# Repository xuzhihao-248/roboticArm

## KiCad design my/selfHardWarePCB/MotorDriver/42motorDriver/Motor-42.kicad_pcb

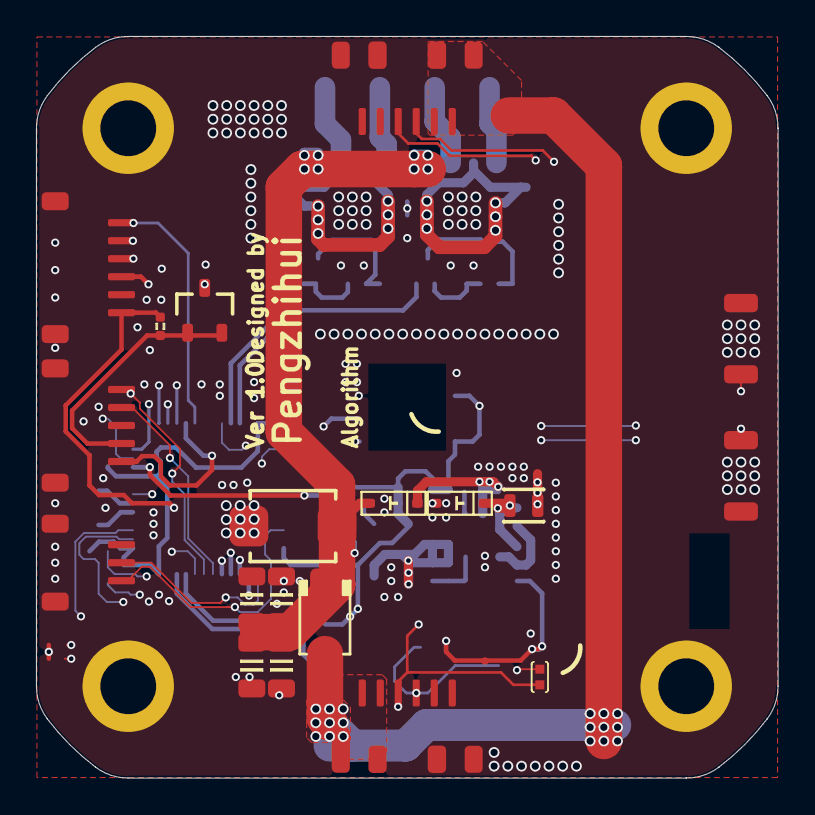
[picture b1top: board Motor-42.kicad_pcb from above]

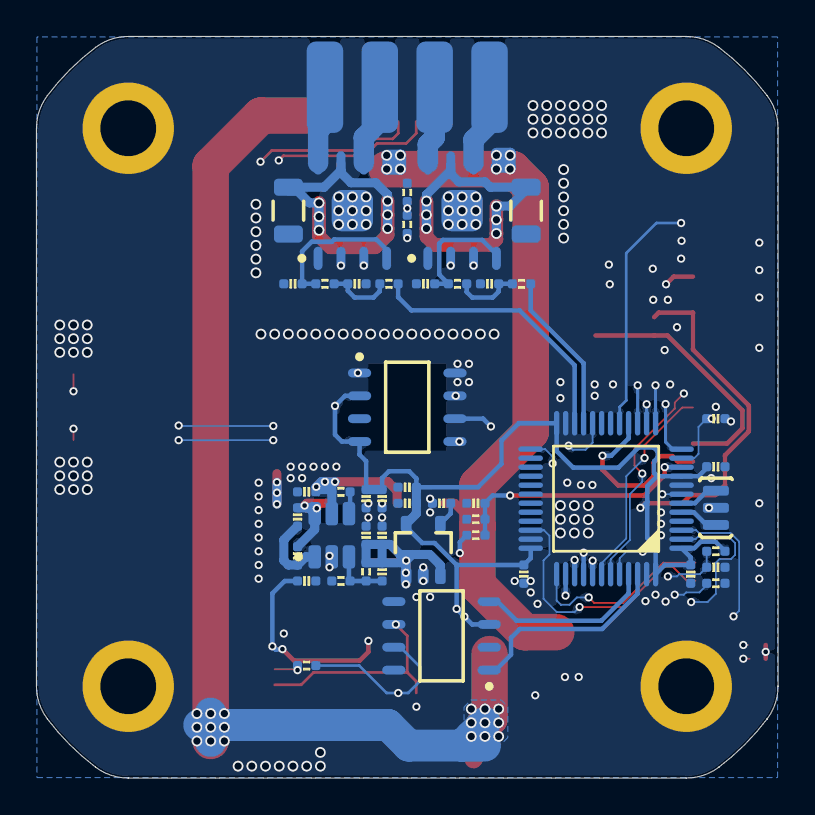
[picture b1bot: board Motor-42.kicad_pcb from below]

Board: 4 copper layers, 41.2 x 41.2 mm, 67 parts (46 on the bottom side), 47 nets.

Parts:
C1, C2, C4, C5, C6, C7, C8, C9, C15, C17, C18, C21, C25, C26: 0.1uF; CAP_0402
C3, C10, C19, C22, C24: 10uF; CAP_0402
C11, C12, C13, C14: 100uF; 1206-CAP
C16: 100pF; CAP_0402
C20: 10uF/50V; CAP_0402
C23: 10nF; CAP_0402
D1: SS54; DO-214AC
D2: SMBJ28CA; SMBJ-CA_MFG
D3, D4: 二极管-5819W; SOD-323
J1: 跳线; 0402-0R
K1, K2: TACT 2P; ButtonTACT_3x4x2_180
L1: 6.8uH; IND-201612
P1: SH1.0-5P
P2, P3, P4: SH1.0-6P
P5: SH1.0-3P
R1, R2, R6, R7, R17: 1K; RES_0402
R3, R8: 0.1R; 1206-RES
R4: NCP15XH103F03RC; RES_0402
R5: 3.3K; RES_0402
R9, R10, R13, R16: 10K; RES_0402
R11, R12: 120R; RES_0402
R14: 1.8K; RES_0402
R15: 1M; RES_0402
T1, T2: 测试点; TEST_PT
U1, U2: TB67H450FNG; SO-8-PAD
U3: STM32F103CBT6; LQFP-48
U4: TL431IDBZT; SOT23-3
U5: SN65HVD232D; SO-8
U6: ME3116; SOT23-6
U7: LP2992 3V3; SOT23-5
U8: MT6816; SO-8
Y1: 12MHz; 晶振-3P

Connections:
ADC_ENC: P1.5, U3.16
BUTTON_1: K1.2, U3.25
BUTTON_2: K2.2, U3.20
CAN_H: P2.4, P3.4, R12.1, U5.7
CAN_L: J1.2, P2.3, P3.3, U5.6
CAN_RX: U3.45, U5.4
CAN_TX: U3.46, U5.1
GND: C1.1, C2.1, C3.1, C4.1, C5.1, C6.1, C7.1, C8.1, C9.1, C10.1, C11.1, C12.1, C13.1, C14.1, C18.1, C19.1, C20.1, C21.1, C22.1, C23.1, C24.1, C25.1, C26.1, D2.1, D3.1, K1.1, K2.1, P1.3, P1.SH1, P1.SH2, P2.5, P2.6, P2.SH2, P3.5, P3.6, P3.SH2, P4.5, P4.SH1, P4.SH2, P5.1, P5.SH1, P5.SH2, R3.2, R5.1, R8.2, R9.2, R14.1, R17.2, U1.1, U1.9, U2.1, U2.9, U3.8, U3.23, U3.35, U3.47, U4.3, U5.2, U6.2, U7.2, U8.8, Y1.2
IN_AM: U1.2, U3.14
IN_AP: U1.3, U3.15
IN_BM: U2.2, U3.12
IN_BP: U2.3, U3.13
IN_PWM_A: R1.1, U3.22
IN_PWM_B: R6.1, U3.21
MT6816_AUX_CS: P4.1, U3.17
MT6816_CS: U3.38, U8.1
NetC1_2: C1.2, R1.2, R2.1
NetC4_2: C4.2, R6.2, R7.1
NetC9_2: C9.2, R10.1, U3.7
NetC15_1: C15.1, C17.1, D3.2, L1.1, U6.6
NetC15_2: C15.2, C17.2, U6.1
NetC16_2: C16.2, R13.1, R14.2, U6.3
NetC20_2: C20.2, D4.2, R15.1, U6.5
NetC23_2: C23.2, U7.4
NetJ1_1: J1.1, R12.2
NetP1_4: P1.4, R11.2, U4.1, U4.2
NetR3_1: R3.1, U1.7
NetR8_1: R8.1, U2.7
NetR9_1: R9.1, U3.44
NetR15_2: R15.2, U6.4
NetU3_5: U3.5, Y1.3
NetU3_6: U3.6, Y1.1
POWER_U: C26.2, R16.2, R17.1, U3.10
SPI1_MISO: P4.2, U3.40, U8.6
SPI1_MOSI: P4.3, U3.41, U8.5
SPI1_SCK: P4.4, U3.39, U8.7
SWCLK: P5.2, U3.37
SWDIO: P5.3, U3.34
TEMP: C3.2, R4.1, R5.2, U3.11
UART1_RX: P1.1, U3.43
UART1_TX: P1.2, U3.42
VCC: C11.2, C12.2, C13.2, C14.2, D1.2, D2.2, D4.1, R16.1, U1.5, U2.5
VCC_3V3: C6.2, C7.2, C8.2, C10.2, C21.2, C22.2, C24.2, C25.2, P4.6, R4.2, R10.2, R11.1, T2.0, U3.1, U3.9, U3.24, U3.36, U3.48, U5.3, U7.5, U8.2, U8.4
VCC_5V: C16.1, C18.2, C19.2, L1.2, R13.2, T1.0, U7.1, U7.3
VCC_IN: D1.1, P2.1, P2.2, P2.SH1, P3.1, P3.2, P3.SH1
VREF_A: C2.2, R2.2, U1.4
VREF_B: C5.2, R7.2, U2.4

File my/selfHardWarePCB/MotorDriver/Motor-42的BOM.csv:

Reference,Qty,Value,DNP,Exclude from BOM,Exclude from Board,Footprint,Datasheet
1?,1,OLED-12880,,,,OLED-12880,
"C1,C2,C4,C5,C6,C7,C8,C9,C15,C17,C18,C21,C25,C26,C32",15,0.1uF,,,,CAP_0402,
"C3,C10,C19,C22,C24,C28,C30",7,10uF,,,,CAP_0402,
"C11,C12,C13,C14",4,100uF,,,,1206-CAP,
C16,1,100pF,,,,CAP_0402,
C20,1,10uF/50V,,,,CAP_0402,
C23,1,10nF,,,,CAP_0402,
C33,1,220pF,,,,CAP_0402,
D1,1,SS54,,,,DO-214AC,
D2,1,SMBJ28CA,,,,SMBJ-CA_MFG,
"D3,D4",2,二极管-5819W,,,,SOD-323,
D6,1,二极管-5B5819WS,,,,SOD-323,
J1,1,跳线,,,,0402-0R,
"K1,K2",2,TACT 2P,,,,ButtonTACT_3x4x2_180,
L1,1,6.8uH,,,,IND-201612,
L2,1,2.2uH,,,,2520-L,
P1,1,SH1.0-5P,,,,SH1.0-5P,
"P2,P3,P4",3,SH1.0-6P,,,,SH1.0-6P,
P5,1,SH1.0-3P,,,,SH1.0-3P,
"R1,R2,R6,R7,R17",5,1K,,,,RES_0402,
"R3,R8",2,0.1R,,,,1206-RES,
R4,1,NCP15XH103F03RC,,,,RES_0402,
R5,1,3.3K,,,,RES_0402,
"R9,R10,R13,R16",4,10K,,,,RES_0402,
"R11,R12",2,120R,,,,RES_0402,
R14,1,1.8K,,,,RES_0402,
R15,1,1M,,,,RES_0402,
R23,1,560K,,,,RES_0402,
R26,1,93.1K,,,,RES_0402,
R27,1,13.3K,,,,RES_0402,
"T1,T2",2,测试点,,,,TEST_PT,
"U1,U2",2,TB67H450FNG,,,,SO-8-PAD,
U3,1,STM32F103CBT6,,,,LQFP-48,
U4,1,TL431IDBZT,,,,SOT23-3,
U5,1,SN65HVD232D,,,,SO-8,
U6,1,ME3116,,,,SOT23-6,
U7,1,LP2992 3V3,,,,SOT23-5,
U8,1,MT6816,,,,SO-8,
U11,1,TPS61040DBV,,,,SOT23-5,
Y1,1,12MHz,,,,晶振-3P,

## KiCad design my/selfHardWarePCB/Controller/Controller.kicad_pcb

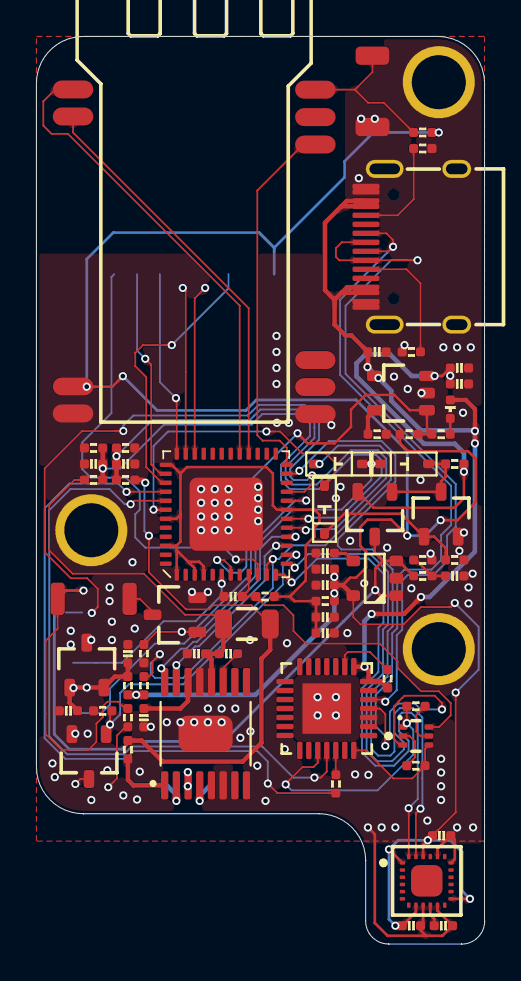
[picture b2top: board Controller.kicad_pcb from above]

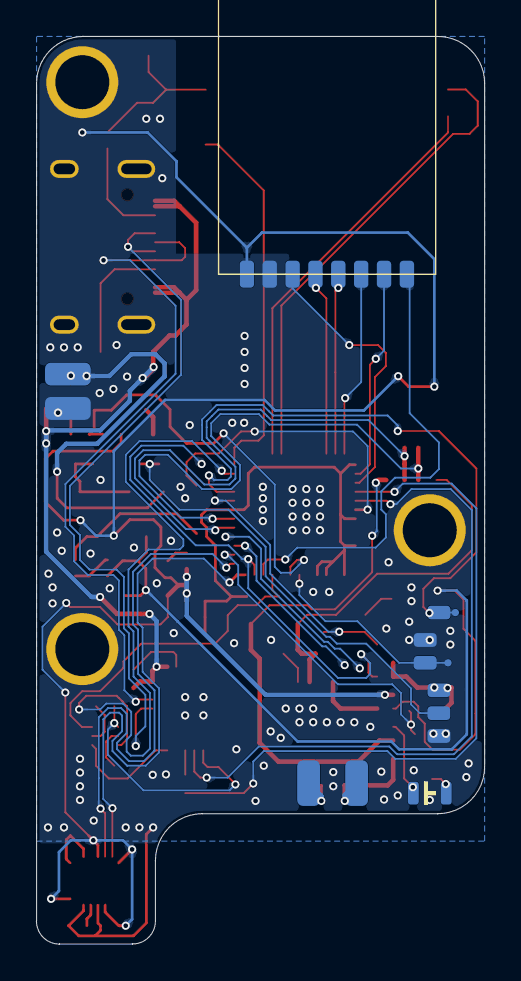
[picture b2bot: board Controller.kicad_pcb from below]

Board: 2 copper layers, 24.9 x 50.4 mm, 71 parts (4 on the bottom side), 60 nets.

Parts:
C1, C5, C13, C15, C17, C19: 0.1uF; CAP_0402
C2, C6, C7, C8, C9, C11, C12, C14, C18: 10uF; CAP_0402
C3: 2.2uF; CAP_0402
C4, C10, C16: 10nF; CAP_0402
C20: 1uF; CAP_0402
D1, D2, D3: 二极管-5819W; SOD-323
D4: color?; LED_0402_RED
D5: color?; LED_0805_RED
K1: TACT 2P; ButtonTACT_3x4x2_180
Q1: AO3401A; SOT23-3
Q2, Q4, Q5: AO3400A; SOT23-3
Q3: BC847BVC-7; SOT563-6
R1, R8, R9, R17, R22, R23, R25, R26, R27: 10K; RES_0402
R2, R4: 100K; RES_0402
R3, R5, R6, R13: 20K; RES_0402
R7: 200R; RES_0402
R10, R24: 47K; RES_0402
R11: 120R; RES_0402
R12: 1R; 1206-RES
R14: 2K; RES_0402
R15, R18: 12K; RES_0402
R16: 1K; RES_0402
R19, R20: 5.1K; RES_0402
R21: 0R; RES_0402
T1, T2: 测试点; TEST_PT
U1: CP2102; QFN-28
U2: LP2992 3V3; SOT23-5
U3: DRV8833PW; TSSOP-16
U4: TL431IDBZT; SOT23-3
U5: MCP73831T; SOT23-5
U6: MPU9250; QFN-24-3x3
U7: DET402
U8: HC-06; 蓝牙模块HC-06
U9: NRF24L01; NRF24L01-MODULE
U10: ESP32_SIP; QFN-48_7X7
USB1: Type-C; Type-C-TOP

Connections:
3V3A: C18.2, C19.2, R21.2, R25.1, U10.1, U10.3, U10.4, U10.19, U10.37, U10.43, U10.46
BAT_DET_1: C5.2, R2.1, R4.2
BOOT_1: Q3.3, U10.23
BT_SET_1: K1.1, R24.2, U8.34
BUZZ_1: Q4.1, R26.2, U10.20
CHG_DET_1: R16.2, R17.1, U5.1, U10.7
CP_Rx_1: U1.25, U10.41
CP_Tx_1: R7.1, U10.40
DTR_1: Q3.4, R15.1, U1.28
EC_KEY_1: D1.2, D2.2
EC_KEY_DET_1: D2.1, R22.2, U10.11
ESP_EN_1: C20.1, Q3.6, R25.2, U10.9
GND: C1.1, C2.1, C3.1, C4.1, C5.1, C6.1, C7.1, C8.1, C9.1, C11.1, C12.1, C13.1, C14.1, C15.2, C16.2, C17.1, C18.1, C19.1, C20.2, K1.2, Q2.2, Q4.2, Q5.2, R4.1, R8.1, R9.1, R13.1, R14.2, R19.1, R20.2, R26.1, R27.1, U1.3, U1.29, U2.2, U3.3, U3.6, U3.13, U3.PAD, U4.3, U5.2, U6.9, U6.11, U6.18, U6.20, U8.13, U8.22, U9.2, U10.49, USB1.1, USB1.2, USB1.3, USB1.4, USB1.A1, USB1.A12, USB1.B1, USB1.B12
GPIO4_1: U8.32, U10.24
GPIO5_1: U9.4, U10.34
GPIO9_1: U8.2, U10.28
GPIO10_1: U8.1, U10.29
GPIO12_1: C7.2, R6.1, R9.2, U10.18
GPIO14_1: C6.2, R5.1, R8.2, U10.17
GPIO15_1: T2.0, U10.21
GPIO18_1: U9.5, U10.35
GPIO19_1: U9.7, U10.38
GPIO21_1: D3.1, U10.42
GPIO22_1: U9.3, U10.39
GPIO23_1: U9.6, U10.36
GPIO25_1: Q5.1, R27.2, U10.14
GPIO26_1: U3.15, U10.15
GPIO27_1: U3.16, U10.16
GPIO32_1: U6.24, U10.12
GPIO33_1: U6.23, U10.13
GPIO34_1: U9.8, U10.10
GPIO37_1: T1.0, U10.6
NetC3_2: C3.2, U3.14
NetC4_2: C4.2, U2.4
NetC10_2: C10.2, U3.11
NetC17_2: C17.2, U6.10
NetD1_1: D1.1, Q1.1, Q2.3, R3.2
NetD3_2: D3.2, Q2.1, R13.2
NetD4_2: D4.2, R16.1
NetD5_1: D5.1, R23.1
NetD5_2: D5.2, Q5.3
NetQ3_2: Q3.2, R15.2
NetQ3_5: Q3.5, R18.2
NetQ4_3: Q4.3, U7.2
NetR1_2: R1.2, U1.9
NetR7_2: R7.2, U1.26
NetR10_1: R10.1, U3.1
NetR14_1: R14.1, U5.5
NetR19_2: R19.2, USB1.B5
NetR20_1: R20.1, USB1.A5
RTS_1: Q3.1, R18.1, U1.24
SENSE_1_N: C10.1, C11.2, R6.2, R12.1, U3.12
USB-PWR-DM_1: U1.5, USB1.A7, USB1.B7
USB-PWR-DP_1: U1.4, USB1.A6, USB1.B6
VBAT: Q1.3, R2.2, R23.2, U2.1, U2.3, U7.1
VBAT_IN: C12.2, C13.2, Q1.2, R3.1, U5.3
VCC_3V3: C1.2, C2.2, C15.1, C16.1, R11.1, R17.2, R21.1, R22.1, R24.1, U2.5, U6.1, U6.8, U6.13, U6.22, U8.12, U9.1
VCC_5V: R5.2, R10.2, R12.2
VREF_2V5: C8.2, C9.2, R11.2, U4.1, U4.2
VUSB: C14.2, D4.1, R1.1, U1.7, U1.8, U5.4, USB1.A4, USB1.A9, USB1.B4, USB1.B9

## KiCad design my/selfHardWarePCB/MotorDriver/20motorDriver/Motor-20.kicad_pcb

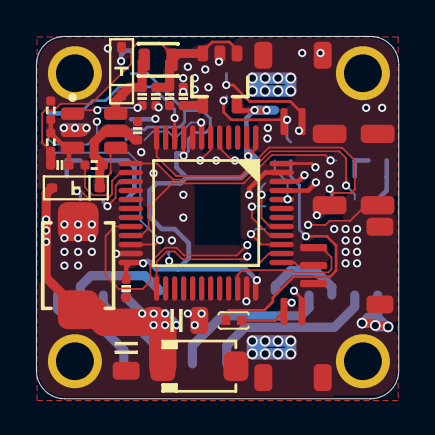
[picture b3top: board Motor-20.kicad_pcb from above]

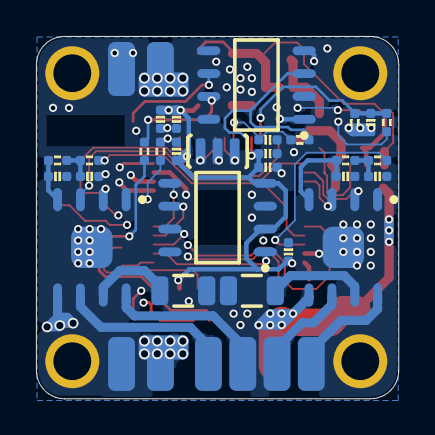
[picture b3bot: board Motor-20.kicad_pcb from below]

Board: 4 copper layers, 20.1 x 20.1 mm, 54 parts (28 on the bottom side), 40 nets.

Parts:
C1, C2, C3, C4, C5, C6, C7, C8, C11, C15, C16, C20, C21: 0.1uF; CAP_0402
C9, C10: 100uF; 1206-CAP
C12, C17, C18, C19: 10uF; CAP_0402
C13: 10nF; CAP_0402
C14: 100pF; CAP_0402
D1: SS54; DO-214AC
D2: SMBJ28CA; SMBJ-CA_MFG
D3, D4: 二极管-5819W; SOD-323
J1: 跳线; 0402-0R
K1, K2: TACT 2P; ButtonTACT_3x4x2_180
L1: 6.8uH; IND-201612
P1, P2: SH1.0-2P
P3: SH1.0-3P
R1, R2, R4, R5, R14: 1K; RES_0402
R3, R6: 0.1R; 1206-RES
R7, R8, R10, R13: 10K; RES_0402
R9: 120R; RES_0402
R11: 1.8K; RES_0402
R12: 1M; RES_0402
U1, U2: TB67H450FNG; SO-8-PAD
U3: STM32F103CBT6; LQFP-48
U4: SN65HVD232D; SO-8
U5: LP2992 3V3; SOT23-5
U6: ME3116; SOT23-6
U7: MT6816; SO-8
Y1: 12MHz; 晶振-3P

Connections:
BUTTON_DOWN: K2.2, U3.20
BUTTON_UP: K1.2, U3.25
CAN_H: P1.2, P2.2, R9.1, U4.7
CAN_L: J1.2, P1.1, P2.1, U4.6
CAN_RX: U3.45, U4.4
CAN_TX: U3.46, U4.1
GND: C1.1, C2.1, C3.1, C4.1, C5.1, C6.1, C7.1, C8.1, C9.1, C10.1, C11.1, C12.1, C13.1, C16.1, C17.1, C18.1, C19.1, C20.1, C21.1, D2.1, D3.1, K1.1, K2.1, P1.SH1, P1.SH2, P2.SH1, P2.SH2, P3.1, P3.SH1, P3.SH2, R3.2, R6.2, R7.2, R11.1, R14.2, U1.1, U1.9, U2.1, U2.9, U3.8, U3.23, U3.35, U3.47, U4.2, U5.2, U6.2, U7.8, Y1.2
IN_AM: U1.2, U3.14
IN_AP: U1.3, U3.15
IN_BM: U2.2, U3.12
IN_BP: U2.3, U3.13
IN_PWM_A: R1.1, U3.22
IN_PWM_B: R4.1, U3.21
MT6816_CS: U3.38, U7.1
NetC1_2: C1.2, R1.2, R2.1
NetC3_2: C3.2, R4.2, R5.1
NetC5_2: C5.2, R8.1, U3.7
NetC13_2: C13.2, U5.4
NetC14_2: C14.2, R10.1, R11.2, U6.3
NetC15_1: C15.1, D3.2, L1.1, U6.6
NetC15_2: C15.2, U6.1
NetC18_2: C18.2, D4.2, R12.1, U6.5
NetJ1_1: J1.1, R9.2
NetR3_1: R3.1, U1.7
NetR6_1: R6.1, U2.7
NetR7_1: R7.1, U3.44
NetR12_2: R12.2, U6.4
NetU3_5: U3.5, Y1.3
NetU3_6: U3.6, Y1.1
POWER_U: C21.2, R13.2, R14.1, U3.10
SPI1_MISO: U3.40, U7.6
SPI1_MOSI: U3.41, U7.5
SPI1_SCK: U3.39, U7.7
SWCLK: P3.2, U3.37
SWDIO: P3.3, U3.34
VCC: C9.2, C10.2, D1.2, D2.2, D4.1, R13.1, U1.5, U2.5
VCC_3V3: C6.2, C7.2, C8.2, C11.2, C12.2, C19.2, C20.2, R8.2, U3.1, U3.9, U3.24, U3.36, U3.48, U4.3, U5.5, U7.2, U7.4
VCC_5V: C14.1, C16.2, C17.2, L1.2, R10.2, U5.1, U5.3
VREF_A: C2.2, R2.2, U1.4
VREF_B: C4.2, R5.2, U2.4

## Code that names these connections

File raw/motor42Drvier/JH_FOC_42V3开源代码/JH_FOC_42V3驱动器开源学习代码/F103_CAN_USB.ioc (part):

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Mcu.Name=STM32F103C(8-B)Tx
Mcu.Package=LQFP48
Mcu.UserName=STM32F103C8Tx
PA0-WKUP.Signal=ADCx_IN0
PA1.Signal=GPIO_Input
PA11.Mode=Device
PA11.Signal=USB_DM
PA12.Mode=Device
PA12.Signal=USB_DP
PA13.Mode=Serial_Wire
PA13.Signal=SYS_JTMS-SWDIO
PA14.Mode=Serial_Wire
PA14.Signal=SYS_JTCK-SWCLK
PA15.Signal=S_TIM2_CH1_ETR
PA2.GPIOParameters=GPIO_PuPd,GPIO_Label
PA2.GPIO_Label=RLimit
PA2.GPIO_PuPd=GPIO_PULLDOWN
PA2.Signal=GPIO_Input
PA3.GPIOParameters=GPIO_PuPd,GPIO_Label
PA3.GPIO_Label=Llimit
PA3.GPIO_PuPd=GPIO_PULLDOWN
PA3.Signal=GPIO_Input
PA4.GPIOParameters=GPIO_Label
PA4.GPIO_Label=SPI_CS
PA4.Signal=GPIO_Output
PA5.Mode=Full_Duplex_Master
PA5.Signal=SPI1_SCK
PA6.Mode=Full_Duplex_Master
PA6.Signal=SPI1_MISO
PA7.Mode=Full_Duplex_Master
PA7.Signal=SPI1_MOSI
PB0.Signal=ADCx_IN8
PB1.Signal=ADCx_IN9
PB10.Signal=S_TIM2_CH3
PB11.Signal=S_TIM2_CH4
PB12.GPIOParameters=GPIO_Label
PB12.GPIO_Label=LED
PB12.Signal=GPIO_Output
PB3.Signal=S_TIM2_CH2
PB8.Mode=CAN_Activate
PB8.Signal=CAN_RX
PB9.Mode=CAN_Activate
PB9.Signal=CAN_TX
PD0-OSC_IN.Mode=HSE-External-Oscillator
PD0-OSC_IN.Signal=RCC_OSC_IN
PD1-OSC_OUT.Mode=HSE-External-Oscillator
PD1-OSC_OUT.Signal=RCC_OSC_OUT
RCC.SYSCLKFreq_VALUE=72000000
RCC.SYSCLKSource=RCC_SYSCLKSOURCE_PLLCLK
board=custom

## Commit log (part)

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2026-05-23 初始化，在doc文件中创建指导文档Github协作指南.md
2026-05-23 修改了文档
2026-05-23 加了一些内容在里面
2026-05-23 添加了linux命令行的操作指南
2026-05-23 添加文档recoder.md，方便记录工作流程
2026-05-23 整理了一些资料
2026-05-23 整理文档
2026-05-23 修改了文件
2026-05-23 修改了一些文档
2026-05-24 加入了程序和固件
2026-06-06 在rviz中运行了机械臂的模型
2026-06-06 设置了MoveIt并且成功进行了轨迹规划，遇到的问题和解决方案记载在文档recoder
2026-06-07 git使用测试
2026-06-07 测试完成，恢复原先状态
2026-06-07 规范了git流程
2026-06-07 添加了几个文档，理解原版项目中的固件、软件、电路板
2026-06-07 导出了BOM表
2026-06-07 步进42驱动引脚说明
2026-06-07 增加了bom表
2026-06-07 Add .gitignore
2026-06-08 测量了电机和减速器的关键尺寸
2026-06-08 文档整理
2026-06-08 转移文件至my文件夹下，已保留原始问价raw
2026-06-09 确认了BOM表
2026-06-10 记录了Unity开发上位机的过程
2026-06-11 unityProjectUpdate
2026-06-12 unity上位机的开发
2026-06-15 unity开发上位机
2026-06-16 Unity上位机的开发，详情在Recoder中
2026-06-22 焊好了第一块板子但是stm32不能识别，需要电源验证
